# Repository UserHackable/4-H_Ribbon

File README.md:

The [Cache Makers 4-H Club](http://cachemakers.org) LED Ribbon is a fun way to introduce soldering.
  		  
It does require soldering 20 leds, an 8 pin ATtiny85 microcontroller, a button, and a battery clip. 
## 4-HCloverMedallion 

### Board dimensions

* (200000, 300000) original units
* (2.0000, 3.0000) inches
* (50.8000, 76.2000) mm

| Front | Back |
| --- | --- |
|  |  |

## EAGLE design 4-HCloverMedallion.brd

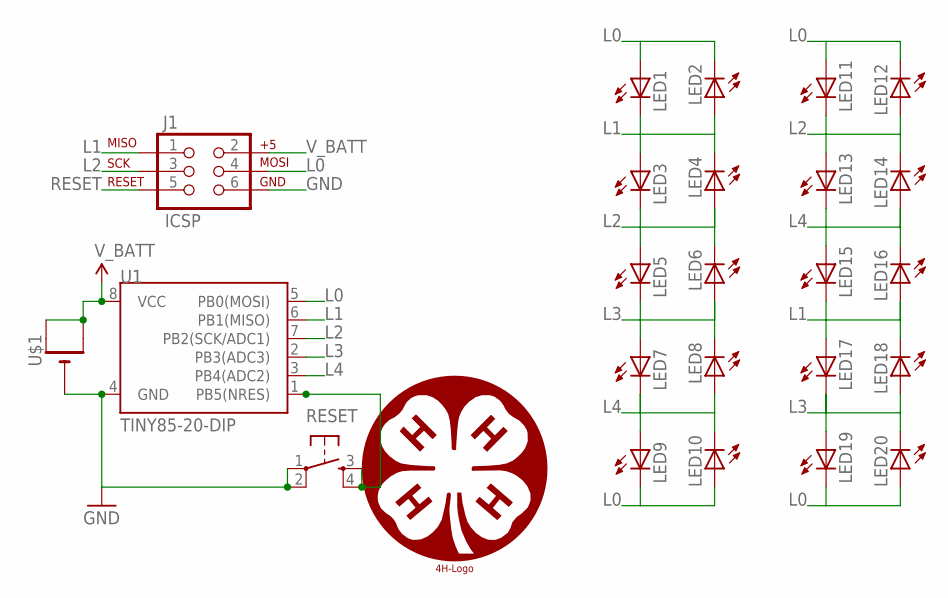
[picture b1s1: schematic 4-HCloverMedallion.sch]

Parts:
J1: ICSP; 2X3-NS
LED1, LED2, LED3, LED4, LED5, LED6, LED7, LED8, LED9, LED10, LED11, LED12, LED13, LED14, LED15, LED16, LED17, LED18, LED19, LED20: LED5MM
RESET: TAC_SWITCHPTH; TACTILE-PTH
U1: TINY85-20-DIP; DIP08
U$1: CR2032THM; CR2032-THRU
U$2: 4H-LOGO14; 4H_LOGO_14

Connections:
GND: J1.6 (GND), RESET.1, RESET.2, U1.4 (GND), U$1.-
L0: J1.4 (MOSI), LED1.A, LED2.K (C), LED9.K (C), LED10.A, LED11.A, LED12.K (C), LED19.K (C), LED20.A, U1.5 (PB0(MOSI))
L1: J1.1 (MISO), LED1.K (C), LED2.A, LED3.A, LED4.K (C), LED15.K (C), LED16.A, LED17.A, LED18.K (C), U1.6 (PB1(MISO))
L2: J1.3 (SCK), LED3.K (C), LED4.A, LED5.A, LED6.K (C), LED11.K (C), LED12.A, LED13.A, LED14.K (C), U1.7 (PB2(SCK/ADC1))
L3: LED5.K (C), LED6.A, LED7.A, LED8.K (C), LED17.K (C), LED18.A, LED19.A, LED20.K (C), U1.2 (PB3(ADC3))
L4: LED7.K (C), LED8.A, LED9.A, LED10.K (C), LED13.K (C), LED14.A, LED15.A, LED16.K (C), U1.3 (PB4(ADC2))
RESET: J1.5 (RST), RESET.3, RESET.4, U1.1 (PB5(NRES))
V_BATT: J1.2 (V+), U1.8 (VCC), U$1.+1 (+), U$1.+2 (+1)

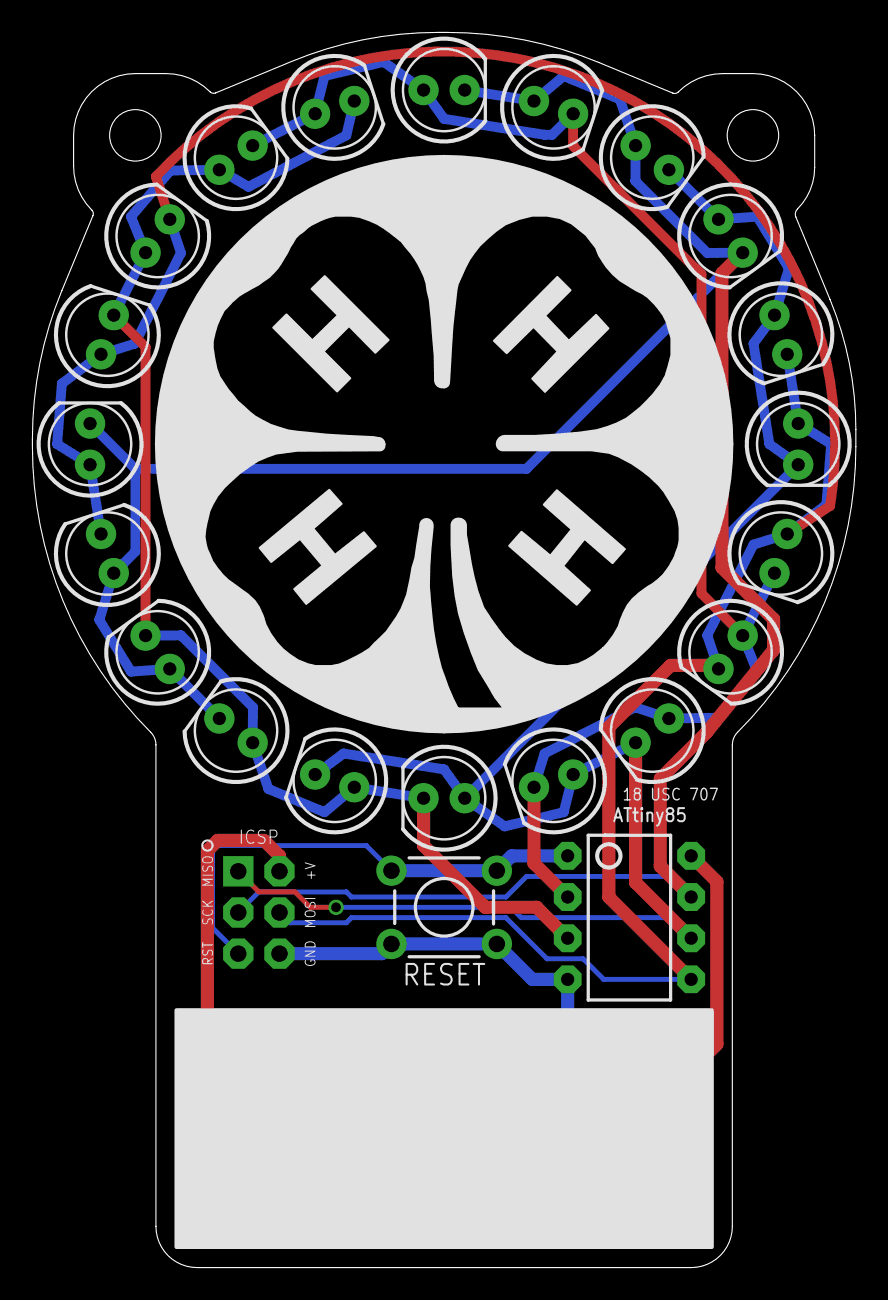
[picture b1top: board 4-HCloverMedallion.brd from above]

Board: 2 copper layers, 50.8 x 76.2 mm, 25 parts (1 on the bottom side), 8 nets.

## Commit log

2016-03-07 updating image
2016-03-07 removing gerber files
2016-03-07 updating gitignore
2016-04-07 updating files
2016-04-07 updte
2016-04-07 updating readme
2016-04-07 updating build result
2016-04-07 updating 18 USC 707
2016-04-07 updating
2016-04-07 from Makefile

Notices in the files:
parts and their libraries:
SparkFun-DigitalIC: Licensing: Creative Commons ShareAlike 4.0 International - https://creativecommons.org/licenses/by-sa/4.0
